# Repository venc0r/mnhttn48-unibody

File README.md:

# mnhTTn48 unibody

Unibody variant of the [mnhTTn48](https://github.com/venc0r/mnhttn) split keyboard,
made to sit on top of a notebook keyboard (Dell XPS 13 9300, MacBook Pro 14 2026).

* mnhTTn48 key positions, reduced to 5x4+2 per side (44 keys), Cherry MX ULP switches, mnhTTn48 keycaps
* Both halves on one PCB, 20 degree splay per half, re-gret style finger splay (pinky 11, ring 4)
* Fits the MacBook Pro 14 keyboard well, clear of Touch ID, speakers and trackpad
* One Seeed XIAO nRF52840 BLE + 74HC595 shift register, 8x6 matrix, ZMK
* 1.6 mm PCB with a flat underside, rests on the deck above the keyboard and on the palm rest
  beside the trackpad, so the notebook keys are never touched

Status: PCB (1.6 mm, with Touch ID window) and parts ordered 2026-11-22, ZMK shield written but not built yet, see [agent.md](agent.md).

## Layout
mnhTTn48 key positions are the source of truth (`tools/keys-mnhttn48.json`, extracted from the
parent board). The generator drops the extra inner key and the innermost thumb key of each
half, fans the finger columns like ergogen does for the
[re-gret](https://github.com/rschenk/re-gret), rotates each half inward around its inner top
corner, centres the result in the notebook's keyboard well (`tools/notebooks.json`) and writes
a 1:1 print for the paper fit test plus the key positions for the board:

```sh
tools/extract_keys.py ../mnhttn/board/mnhttn.kicad_pcb        # only after the parent layout changed
tools/layout.py                                               # docs/images/layout.svg, board/layout.json
tools/layout.py --splay 20 --gap auto --column-splay 11,-7,-4 --thumb-shift 8,1   # the defaults
tools/layout.py --notebook xps13                              # same keys in the XPS 13 envelope
```

`--column-splay` is ergogen style: pinky to inner, each relative to the previous column.
`--gap auto` widens the halves until a key cell would leave the usable area or touch a keep-out
(on the MacBook that is Touch ID). Key cells outside the envelope or inside a keep-out are reported.

Print `docs/images/layout.pdf` at 100 % (A4 landscape, the board outline is centred on the page)
and check both 100 mm rulers (trackpad notch, between the halves), measured from the long tick
at 0 to the long tick at 100. Paper size plain A4, not
"borderless" (that enlarges about 3 %), scale 100 %, not "fit". Print the PDF, not the SVG: the macOS print
dialog shrinks SVGs to the printable area (about 1 %). `tools/svg_to_pdf.py` writes the PDF without
external tools and asks the viewer not to scale it.

## Schematic
Generated, not drawn: `tools/gen_schematic.py` writes the root sheet, the switch sub-sheet and
the project file into [board/](board/). The matrix is one 74HC595 (8 driven columns) x 6 XIAO
inputs, see `tools/matrix.json`. Check with

```sh
tools/gen_schematic.py
kicad-cli sch erc --severity-all board/mnhttn48-unibody.kicad_sch
```

## PCB
Generated as well: `tools/gen_pcb.py` places the switches from `board/layout.json`, the diodes
in two blocks between the halves, the XIAO in the top left corner (USB-C out of the left edge,
reachable while typing), the shift register between the halves and routes the whole matrix. It
needs KiCad's own Python (pcbnew), `tools/drc.sh` wraps generation and DRC:

```sh
tools/drc.sh            # regenerate the board, DRC summary and key matrix check
tools/drc.sh details    # every violation with coordinates
tools/check_matrix.py   # key matrix from the netlist vs tools/matrix.json, prints the grid
```

KiCad 10 project in [board/](board/), footprints in `board/mnhttn.pretty` (copied from mnhTTn48
plus SOIC-16 and 0603 from the KiCad library). 1.6 mm, 2 layers.

Fabrication files for JLCPCB (Gerber X2 with Protel extensions, Excellon drills, settings from
their KiCad guide): `make -C board fab` writes `board/out/` and `board/out.zip` (not tracked).
Order 2 layers, 1.6 mm thickness, 284.3 x 190 mm.

## Parts

| Part | Count | Package / remarks |
| ---- | ----: | ----------------- |
| PCB | 1 | 2 layers, 1.6 mm, 284.3 x 190 mm |
| Seeed Studio XIAO nRF52840 | 1 | BLE version, not the Plus |
| Cherry MX ULP | 44 | |
| 1N4148W | 44 | SOD-123 |
| 74HC595 | 1 | SOIC-16 narrow (3.9 mm), e.g. 74HC595D |
| Capacitor 100 nF | 1 | 0603, X7R, 25 V or more |
| MSK12C02 | 1 | power switch |
| COM-08720 | 1 | reset switch, optional |
| 301030 LiPo | 1 | 3.7 V, 80 mAh, 32 x 10 x 3 mm |
| Keycaps | 44 | mnhTTn48 keycaps |
| Rest pads, rubber strips | | rest pads on the deck and palm rest, strips between the notebook key rows |

## Keycaps
Unchanged, use the [mnhTTn48 keycaps](https://github.com/venc0r/mnhttn/tree/main/keycaps).

## Firmware
ZMK v0.3, shield `mnhttn48_unibody` for the `xiao_ble` board. This repo is a ZMK module
(`zephyr/module.yml`, shield in [zmk-config/boards/shields/mnhttn48_unibody](zmk-config/boards/shields/mnhttn48_unibody/)),
like the re-gret. The shield ships an example keymap, your own keymap lives in your zmk-config.
Add the module to `config/west.yml` there:

```yaml
manifest:
  remotes:
    - name: venc0r
      url-base: https://github.com/venc0r
  projects:
    - name: mnhttn48-unibody
      remote: venc0r
      revision: main
```

and the build to `build.yaml`:

```yaml
include:
  - board: xiao_ble
    shield: mnhttn48_unibody
```

Keymap order: four rows of ten (left pinky to inner, right inner to pinky), then the thumbs left
outer, left inner, right inner, right outer. The 74HC595 drives COL_0..7 (QA..QH), the XIAO reads
ROW_0..5 on D0..D5, `col2row`; SPI on D8 (SCK), D10 (MOSI), D9 (latch as chip select).
`tools/gen_zmk.py` writes the matrix transform and the physical layout (ZMK Studio) from
`board/layout.json` and `tools/matrix.json`, `tools/check_matrix.py` checks the wiring.

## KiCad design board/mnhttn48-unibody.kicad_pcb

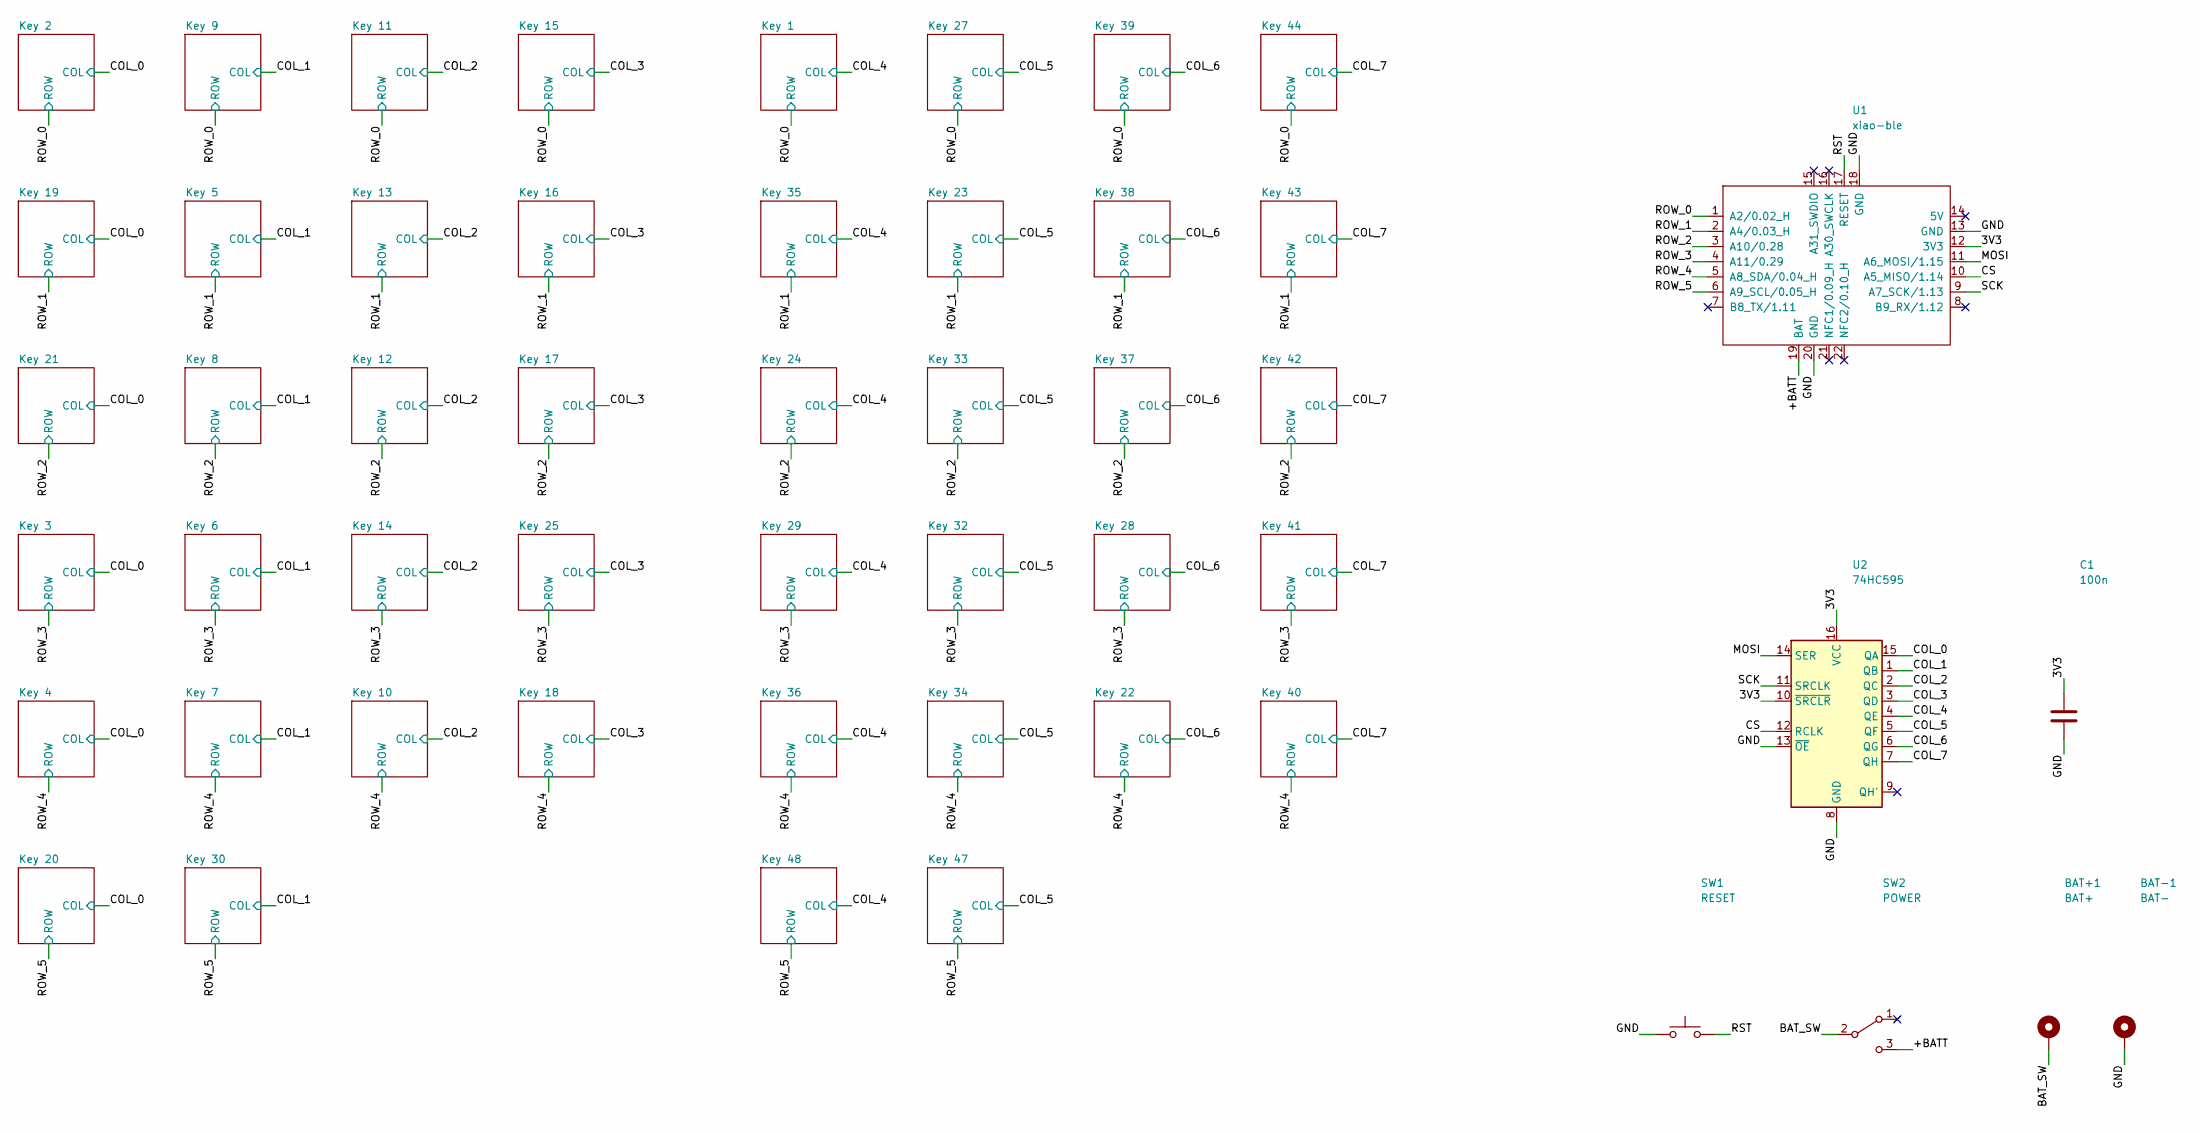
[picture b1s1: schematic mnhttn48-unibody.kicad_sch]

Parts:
BAT+1: BAT+; BatteryPad
BAT-1: BAT-; BatteryPad
C1: 100n; C_0603_1608Metric
SW1: RESET; PushSwitch
SW2: POWER; MSK12C02
U1: xiao-ble; xiao-ble-smd-cutout
U2: 74HC595; SOIC-16_3.9x9.9mm_P1.27mm

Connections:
/3V3: C1.1, U1.12 (3V3), U2.10 (~SRCLR), U2.16 (VCC)
/+BATT: SW2.3 (C), U1.19 (BAT)
/BAT_SW: BAT+1.1, SW2.2 (B)
/COL_0: U2.15 (QA); also elsewhere on the board
/COL_1: U2.1 (QB); also elsewhere on the board
/COL_2: U2.2 (QC); also elsewhere on the board
/COL_3: U2.3 (QD); also elsewhere on the board
/COL_4: U2.4 (QE); also elsewhere on the board
/COL_5: U2.5 (QF); also elsewhere on the board
/COL_6: U2.6 (QG); also elsewhere on the board
/COL_7: U2.7 (QH); also elsewhere on the board
/CS: U1.10 (A5_MISO/1.14), U2.12 (RCLK)
/GND: BAT-1.1, C1.2, SW1.1, U1.13 (GND), U1.18 (GND), U1.20 (GND), U2.8 (GND), U2.13 (~OE)
/MOSI: U1.11 (A6_MOSI/1.15), U2.14 (SER)
/ROW_0: U1.1 (A2/0.02_H); also elsewhere on the board
/ROW_1: U1.2 (A4/0.03_H); also elsewhere on the board
/ROW_2: U1.3 (A10/0.28); also elsewhere on the board
/ROW_3: U1.4 (A11/0.29); also elsewhere on the board
/ROW_4: U1.5 (A8_SDA/0.04_H); also elsewhere on the board
/ROW_5: U1.6 (A9_SCL/0.05_H); also elsewhere on the board
/RST: SW1.2, U1.17 (RESET)
/SCK: U1.9 (A7_SCK/1.13), U2.11 (SRCLK)

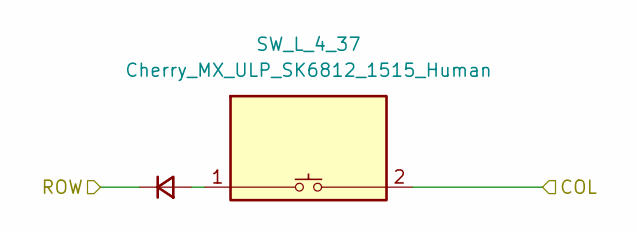
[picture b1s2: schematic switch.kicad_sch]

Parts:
D_L_4_37: 1N4148W; Diode_SOD123
SW_L_4_37: Cherry_MX_ULP_SK6812_1515_Human; Cherry_MX_ULP_Human

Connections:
/COL_6: SW_L_4_37.2; also elsewhere on the board
/ROW_2: D_L_4_37.1 (K); also elsewhere on the board
unnamed: D_L_4_37.2 (A), SW_L_4_37.1

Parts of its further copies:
D_L_4_1, D_L_4_2, D_L_4_3, D_L_4_4, D_L_4_5, D_L_4_6, D_L_4_7, D_L_4_8, D_L_4_9, D_L_4_10, D_L_4_11, D_L_4_12, D_L_4_13, D_L_4_14, D_L_4_15, D_L_4_16, D_L_4_17, D_L_4_18, D_L_4_19, D_L_4_20, D_L_4_21, D_L_4_22, D_L_4_23, D_L_4_24, D_L_4_25, D_L_4_27, D_L_4_28, D_L_4_29, D_L_4_30, D_L_4_32, D_L_4_33, D_L_4_34, D_L_4_35, D_L_4_36, D_L_4_38, D_L_4_39, D_L_4_40, D_L_4_41, D_L_4_42, D_L_4_43, D_L_4_44, D_L_4_47, D_L_4_48: 1N4148W; Diode_SOD123
SW_L_4_1, SW_L_4_2, SW_L_4_3, SW_L_4_4, SW_L_4_5, SW_L_4_6, SW_L_4_7, SW_L_4_8, SW_L_4_9, SW_L_4_10, SW_L_4_11, SW_L_4_12, SW_L_4_13, SW_L_4_14, SW_L_4_15, SW_L_4_16, SW_L_4_17, SW_L_4_18, SW_L_4_19, SW_L_4_20, SW_L_4_21, SW_L_4_22, SW_L_4_23, SW_L_4_24, SW_L_4_25, SW_L_4_27, SW_L_4_28, SW_L_4_29, SW_L_4_30, SW_L_4_32, SW_L_4_33, SW_L_4_34, SW_L_4_35, SW_L_4_36, SW_L_4_38, SW_L_4_39, SW_L_4_40, SW_L_4_41, SW_L_4_42, SW_L_4_43, SW_L_4_44, SW_L_4_47, SW_L_4_48: Cherry_MX_ULP_SK6812_1515_Human; Cherry_MX_ULP_Human

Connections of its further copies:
/COL_0: SW_L_4_2.2, SW_L_4_3.2, SW_L_4_4.2, SW_L_4_19.2, SW_L_4_20.2, SW_L_4_21.2; also elsewhere on the board
/COL_1: SW_L_4_5.2, SW_L_4_6.2, SW_L_4_7.2, SW_L_4_8.2, SW_L_4_9.2, SW_L_4_30.2; also elsewhere on the board
/COL_2: SW_L_4_10.2, SW_L_4_11.2, SW_L_4_12.2, SW_L_4_13.2, SW_L_4_14.2; also elsewhere on the board
/COL_3: SW_L_4_15.2, SW_L_4_16.2, SW_L_4_17.2, SW_L_4_18.2, SW_L_4_25.2; also elsewhere on the board
/COL_4: SW_L_4_1.2, SW_L_4_24.2, SW_L_4_29.2, SW_L_4_35.2, SW_L_4_36.2, SW_L_4_48.2; also elsewhere on the board
/COL_5: SW_L_4_23.2, SW_L_4_27.2, SW_L_4_32.2, SW_L_4_33.2, SW_L_4_34.2, SW_L_4_47.2; also elsewhere on the board
/COL_6: SW_L_4_22.2, SW_L_4_28.2, SW_L_4_38.2, SW_L_4_39.2; also elsewhere on the board
/COL_7: SW_L_4_40.2, SW_L_4_41.2, SW_L_4_42.2, SW_L_4_43.2, SW_L_4_44.2; also elsewhere on the board
/ROW_0: D_L_4_1.1 (K), D_L_4_2.1 (K), D_L_4_9.1 (K), D_L_4_11.1 (K), D_L_4_15.1 (K), D_L_4_27.1 (K), D_L_4_39.1 (K), D_L_4_44.1 (K); also elsewhere on the board
/ROW_1: D_L_4_5.1 (K), D_L_4_13.1 (K), D_L_4_16.1 (K), D_L_4_19.1 (K), D_L_4_23.1 (K), D_L_4_35.1 (K), D_L_4_38.1 (K), D_L_4_43.1 (K); also elsewhere on the board
/ROW_2: D_L_4_8.1 (K), D_L_4_12.1 (K), D_L_4_17.1 (K), D_L_4_21.1 (K), D_L_4_24.1 (K), D_L_4_33.1 (K), D_L_4_42.1 (K); also elsewhere on the board
/ROW_3: D_L_4_3.1 (K), D_L_4_6.1 (K), D_L_4_14.1 (K), D_L_4_25.1 (K), D_L_4_28.1 (K), D_L_4_29.1 (K), D_L_4_32.1 (K), D_L_4_41.1 (K); also elsewhere on the board
/ROW_4: D_L_4_4.1 (K), D_L_4_7.1 (K), D_L_4_10.1 (K), D_L_4_18.1 (K), D_L_4_22.1 (K), D_L_4_34.1 (K), D_L_4_36.1 (K), D_L_4_40.1 (K); also elsewhere on the board
/ROW_5: D_L_4_20.1 (K), D_L_4_30.1 (K), D_L_4_47.1 (K), D_L_4_48.1 (K); also elsewhere on the board
unnamed: D_L_4_1.2 (A), SW_L_4_1.1
unnamed: D_L_4_2.2 (A), SW_L_4_2.1
unnamed: D_L_4_3.2 (A), SW_L_4_3.1
unnamed: D_L_4_4.2 (A), SW_L_4_4.1
unnamed: D_L_4_5.2 (A), SW_L_4_5.1
unnamed: D_L_4_6.2 (A), SW_L_4_6.1
unnamed: D_L_4_7.2 (A), SW_L_4_7.1
unnamed: D_L_4_8.2 (A), SW_L_4_8.1
unnamed: D_L_4_9.2 (A), SW_L_4_9.1
unnamed: D_L_4_10.2 (A), SW_L_4_10.1
unnamed: D_L_4_11.2 (A), SW_L_4_11.1
unnamed: D_L_4_12.2 (A), SW_L_4_12.1
unnamed: D_L_4_13.2 (A), SW_L_4_13.1
unnamed: D_L_4_14.2 (A), SW_L_4_14.1
unnamed: D_L_4_15.2 (A), SW_L_4_15.1
unnamed: D_L_4_16.2 (A), SW_L_4_16.1
unnamed: D_L_4_17.2 (A), SW_L_4_17.1
unnamed: D_L_4_18.2 (A), SW_L_4_18.1
unnamed: D_L_4_19.2 (A), SW_L_4_19.1
unnamed: D_L_4_20.2 (A), SW_L_4_20.1
unnamed: D_L_4_21.2 (A), SW_L_4_21.1
unnamed: D_L_4_22.2 (A), SW_L_4_22.1
unnamed: D_L_4_23.2 (A), SW_L_4_23.1
unnamed: D_L_4_24.2 (A), SW_L_4_24.1
unnamed: D_L_4_25.2 (A), SW_L_4_25.1
unnamed: D_L_4_27.2 (A), SW_L_4_27.1
unnamed: D_L_4_28.2 (A), SW_L_4_28.1
unnamed: D_L_4_29.2 (A), SW_L_4_29.1
unnamed: D_L_4_30.2 (A), SW_L_4_30.1
unnamed: D_L_4_32.2 (A), SW_L_4_32.1
unnamed: D_L_4_33.2 (A), SW_L_4_33.1
unnamed: D_L_4_34.2 (A), SW_L_4_34.1
unnamed: D_L_4_35.2 (A), SW_L_4_35.1
unnamed: D_L_4_36.2 (A), SW_L_4_36.1
unnamed: D_L_4_38.2 (A), SW_L_4_38.1
unnamed: D_L_4_39.2 (A), SW_L_4_39.1
unnamed: D_L_4_40.2 (A), SW_L_4_40.1
unnamed: D_L_4_41.2 (A), SW_L_4_41.1
unnamed: D_L_4_42.2 (A), SW_L_4_42.1
unnamed: D_L_4_43.2 (A), SW_L_4_43.1
unnamed: D_L_4_44.2 (A), SW_L_4_44.1
unnamed: D_L_4_47.2 (A), SW_L_4_47.1
unnamed: D_L_4_48.2 (A), SW_L_4_48.1

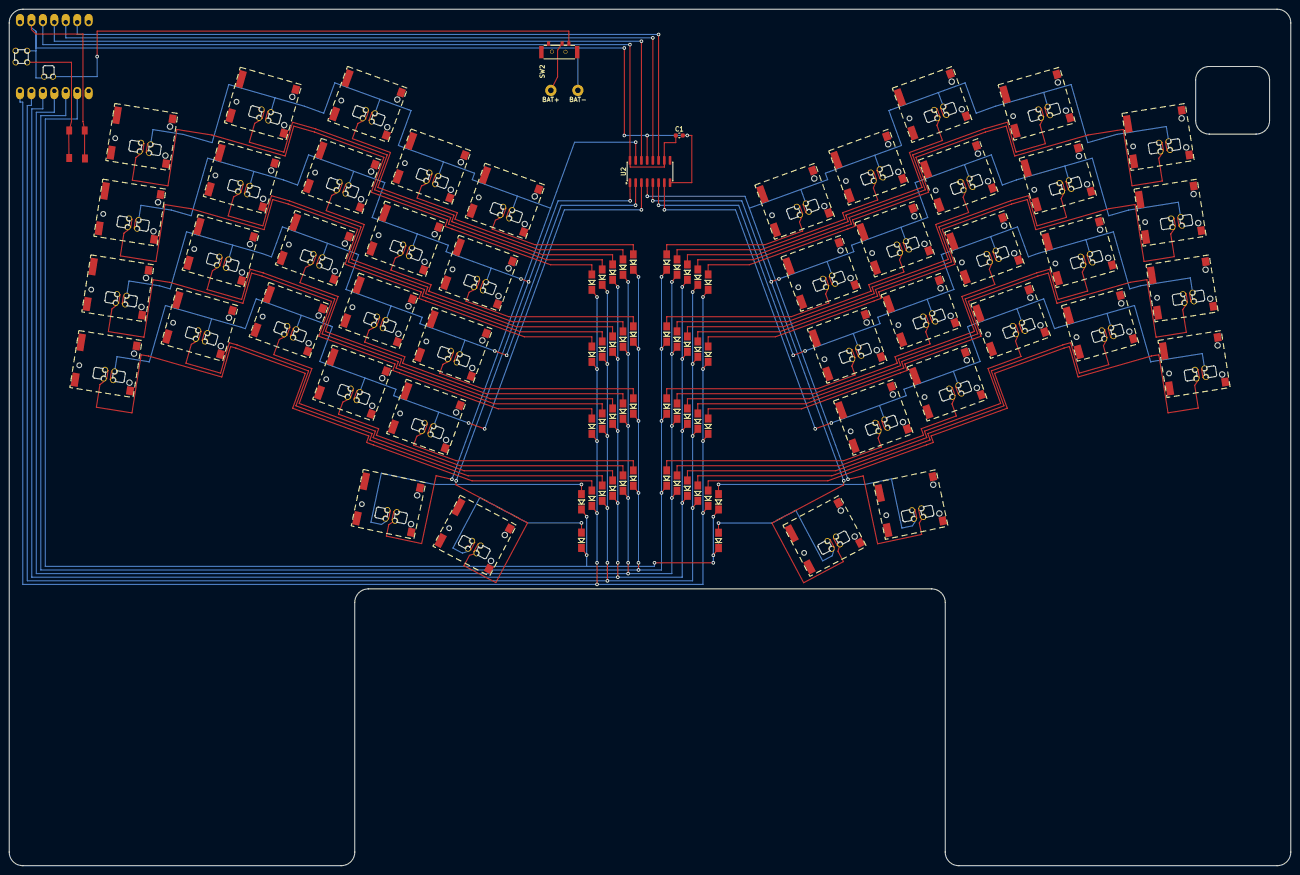
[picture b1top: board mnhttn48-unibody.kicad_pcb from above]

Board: 2 copper layers, 284.3 x 190.0 mm, 95 parts (0 on the bottom side), 66 nets.
